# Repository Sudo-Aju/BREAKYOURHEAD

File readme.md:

<div align="center">

# BYH MacroPad

### A custom 6-key macropad built for professional video editing workflows.

<br>

</div>

---

# Overview

BYH is a compact **6-key mechanical macropad** designed specifically for video editors using applications like **Adobe Premiere Pro** and **DaVinci Resolve**.

Rather than relying on keyboard shortcuts, BYH places the most frequently used editing functions beneath your fingertips while providing two precision rotary encoders for intuitive timeline control.

The device runs **QMK Firmware**, allowing every key, encoder, and layer to be fully customizable.

---

# Features

- 6-key mechanical layout
- Dual EC11 rotary encoders
- 0.91" OLED display
- QMK Firmware
- Layer switching
- Custom PCB
- Silent linear mechanical switches
- Heavy aluminum encoder knobs
- Ergonomic 5–7° angled case
- USB-C connectivity

---

# Hardware

| Component | Specification |
|-----------|---------------|
| **Microcontroller** | Seeed Studio XIAO RP2040 |
| **Keys** | 6 × Cherry MX Mechanical Switches |
| **Encoders** | 2 × EC11 Rotary Encoders |
| **Display** | 0.91" OLED (I²C) |
| **Firmware** | QMK |
| **PCB** | Custom FR4 PCB |
| **Case** | 3D Printed |
| **Connection** | USB-C |

---

# Layers

## Layer 0 — Rough Cut

Primary editing controls.

| Control | Function |
|---------|----------|
| Keys | Cut, Ripple Delete, Undo, Redo, Play/Pause, Marker |
| Left Encoder | Timeline Scrub |
| Right Encoder | Timeline Zoom |

---

## Layer 1 — Color & Audio

Color grading and audio adjustments.

| Control | Function |
|---------|----------|
| Keys | Color Wheels, Curves, Gain, Saturation, Audio Tools |
| Left Encoder | Parameter Adjustment |
| Right Encoder | Fine Control |

---

# Bill of Materials

| Part | Qty | Specification |
|------|----:|---------------|
| Seeed Studio XIAO RP2040 | 1 | Microcontroller |
| 0.91" OLED Display | 1 | I²C |
| EC11 Rotary Encoder | 2 | Push-button |
| Cherry MX Switch | 6 | Linear |
| DSA 1u Keycaps | 6 | Low Profile |
| Custom PCB | 1 | FR4 |
| 1N4148 Diodes | 6 | Through-hole |
| M3 Heat-set Inserts | 5 | Brass |
| M3×12 SHCS Screws | 2 | Steel |
| M3×16 SHCS Screws | 3 | Steel |

---

# Gallery

---

# Why BYH?

Traditional keyboards force editors to remember dozens of shortcuts.

BYH transforms the most frequently used editing commands into dedicated tactile controls, reducing hand movement while improving speed and workflow efficiency.

---

# Future Improvements

- RGB lighting
- Wireless mode
- VIA compatibility
- Multiple OLED pages
- Application auto-detection
- Additional editing profiles

---

<div align="center">

### Designed for creators who spend more time editing than searching for shortcuts.

</div>

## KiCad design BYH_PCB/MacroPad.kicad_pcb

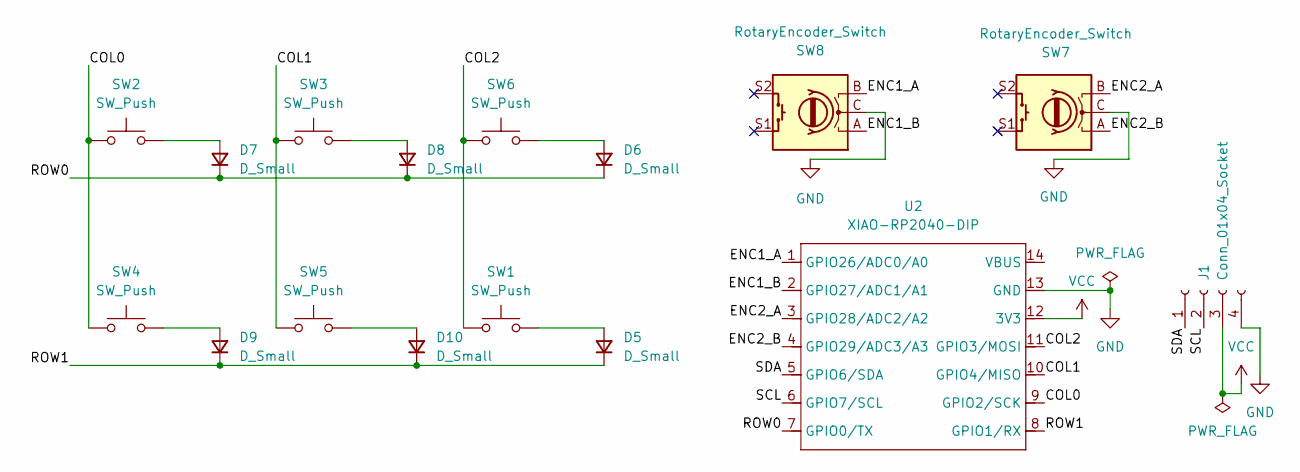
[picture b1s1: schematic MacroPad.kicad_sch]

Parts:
D5, D6, D7, D8, D9, D10: D_Small; D_DO-35_SOD27_P7.62mm_Horizontal
J1: Conn_01x04_Socket; FanPinHeader_1x04_P2.54mm_Vertical
SW1, SW2, SW3, SW4, SW5, SW6: SW_Push; SW_Cherry_MX_1.00u_PCB
SW7, SW8: RotaryEncoder_Switch; RotaryEncoder_Alps_EC11E-Switch_Vertical_H20mm
U2: XIAO-RP2040-DIP

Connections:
/COL0: SW2.1, SW4.1, U2.9 (GPIO2/SCK)
/COL1: SW3.1, SW5.1, U2.10 (GPIO4/MISO)
/COL2: SW1.1, SW6.1, U2.11 (GPIO3/MOSI)
/ENC1_A: SW8.B, U2.1 (GPIO26/ADC0/A0)
/ENC1_B: SW8.A, U2.2 (GPIO27/ADC1/A1)
/ENC2_A: SW7.B, U2.3 (GPIO28/ADC2/A2)
/ENC2_B: SW7.A, U2.4 (GPIO29/ADC3/A3)
/ROW0: D6.1 (K), D7.1 (K), D8.1 (K), U2.7 (GPIO0/TX)
/ROW1: D5.1 (K), D9.1 (K), D10.1 (K), U2.8 (GPIO1/RX)
/SCL: J1.2, U2.6 (GPIO7/SCL)
/SDA: J1.1, U2.5 (GPIO6/SDA)
GND: J1.4, SW7.C, SW8.C, U2.13 (GND)
unnamed: D5.2 (A), SW1.2
unnamed: D6.2 (A), SW6.2
unnamed: D7.2 (A), SW2.2
unnamed: D8.2 (A), SW3.2
unnamed: D9.2 (A), SW4.2
unnamed: D10.2 (A), SW5.2
VCC: J1.3, U2.12 (3V3)

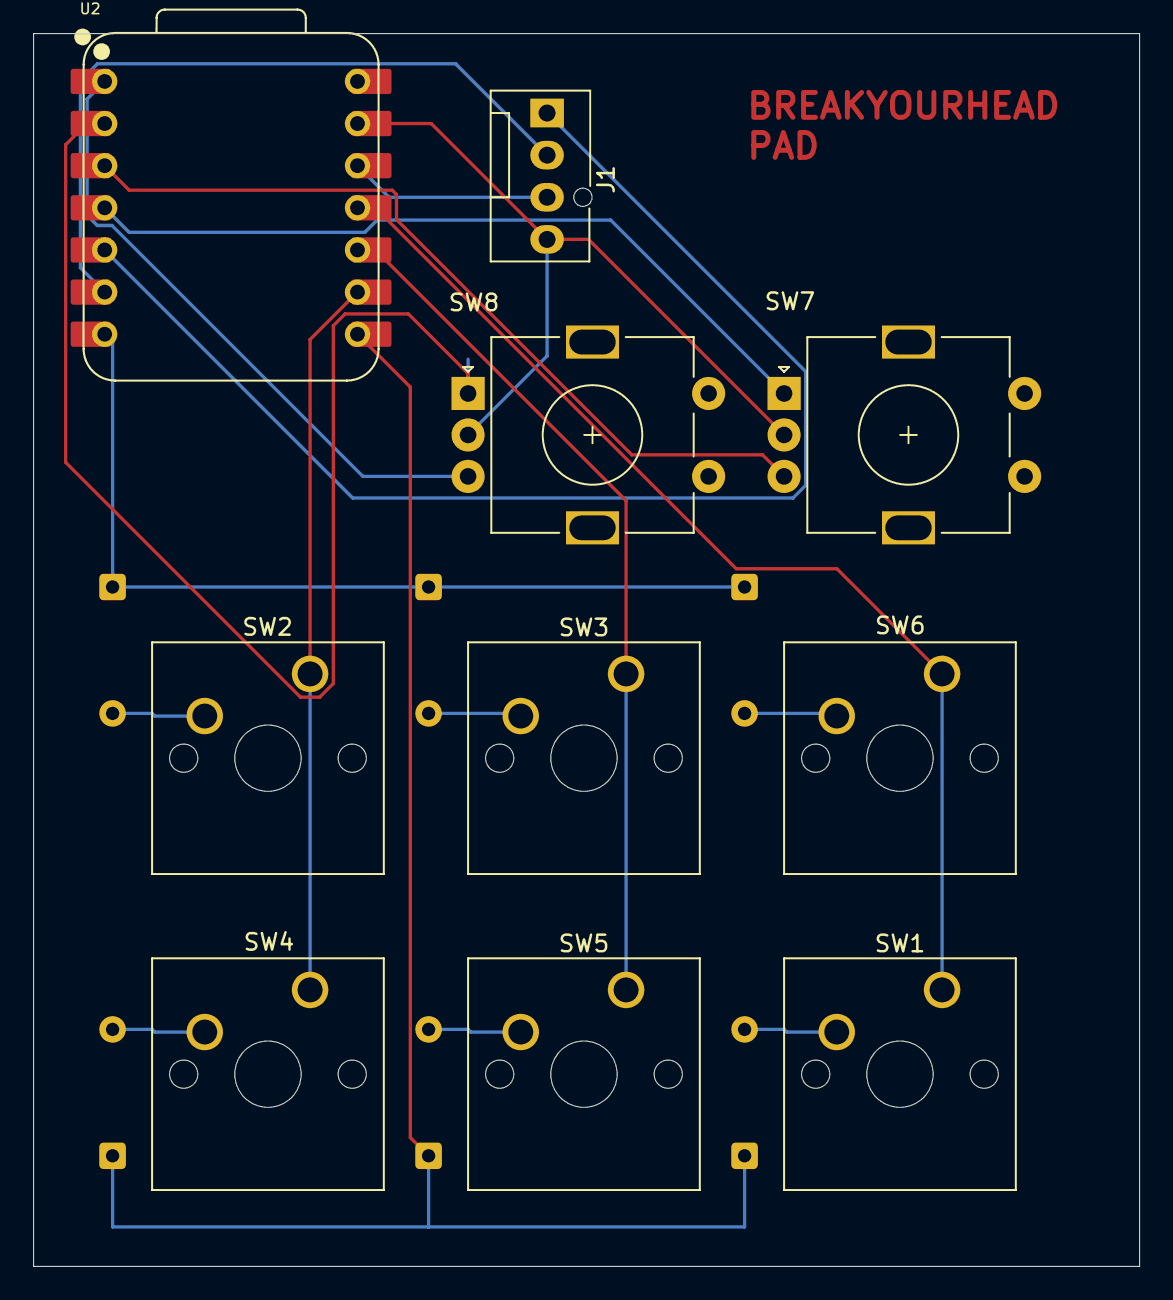
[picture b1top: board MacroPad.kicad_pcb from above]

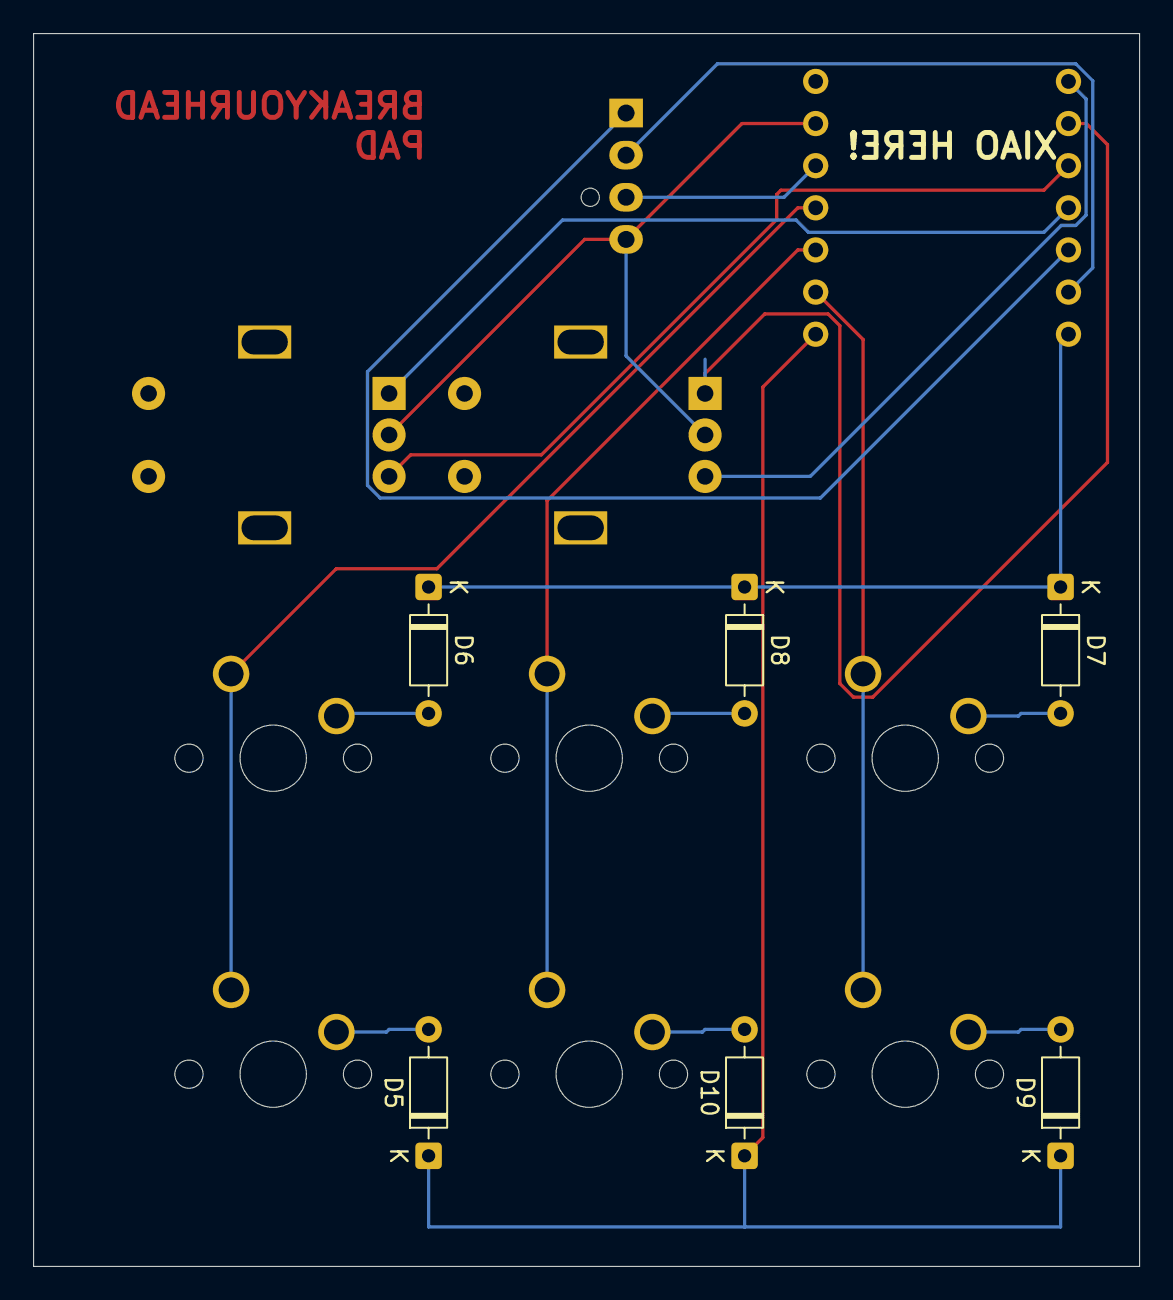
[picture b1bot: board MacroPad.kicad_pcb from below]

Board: 2 copper layers, 66.7 x 74.3 mm, 16 parts (6 on the bottom side), 19 nets.

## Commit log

2025-12-04 Add initial content to readme.md
2025-12-04 Enhance README with project details and instructions
    Expanded README to include detailed project description, BOM, features, build guide, and firmware instructions.
2025-12-04 Update README by removing firmware badge and sections
    Removed firmware badge and additional requirements sections. Updated descriptions for diodes and display components.
2025-12-04 Added firmware
2025-12-04 added images
2025-12-04 Refactor README to HTML format with styling
    Updated the README to include HTML structure and improved styling for better presentation.
2025-12-04 Refactor HTML structure in readme.md
2025-12-04 Enhance README layout and styling
    Updated the README to include additional styling and structure for better presentation.
2025-12-04 Remove main content from README file
    Removed the main content and structure of the README file, including the header, BOM, and gallery sections.
2025-12-04 Adjust image tags in readme for consistent width
    Updated image tags to set width for better layout.
2025-12-04 Improve styling in README for header and gallery
    Updated the styling of the header and gallery sections in the README file. Added inline styles for better presentation.
2025-12-05 Add two new images to the README
2025-12-06 Source design files uploaded
2026-01-27 added the kmk firmware
